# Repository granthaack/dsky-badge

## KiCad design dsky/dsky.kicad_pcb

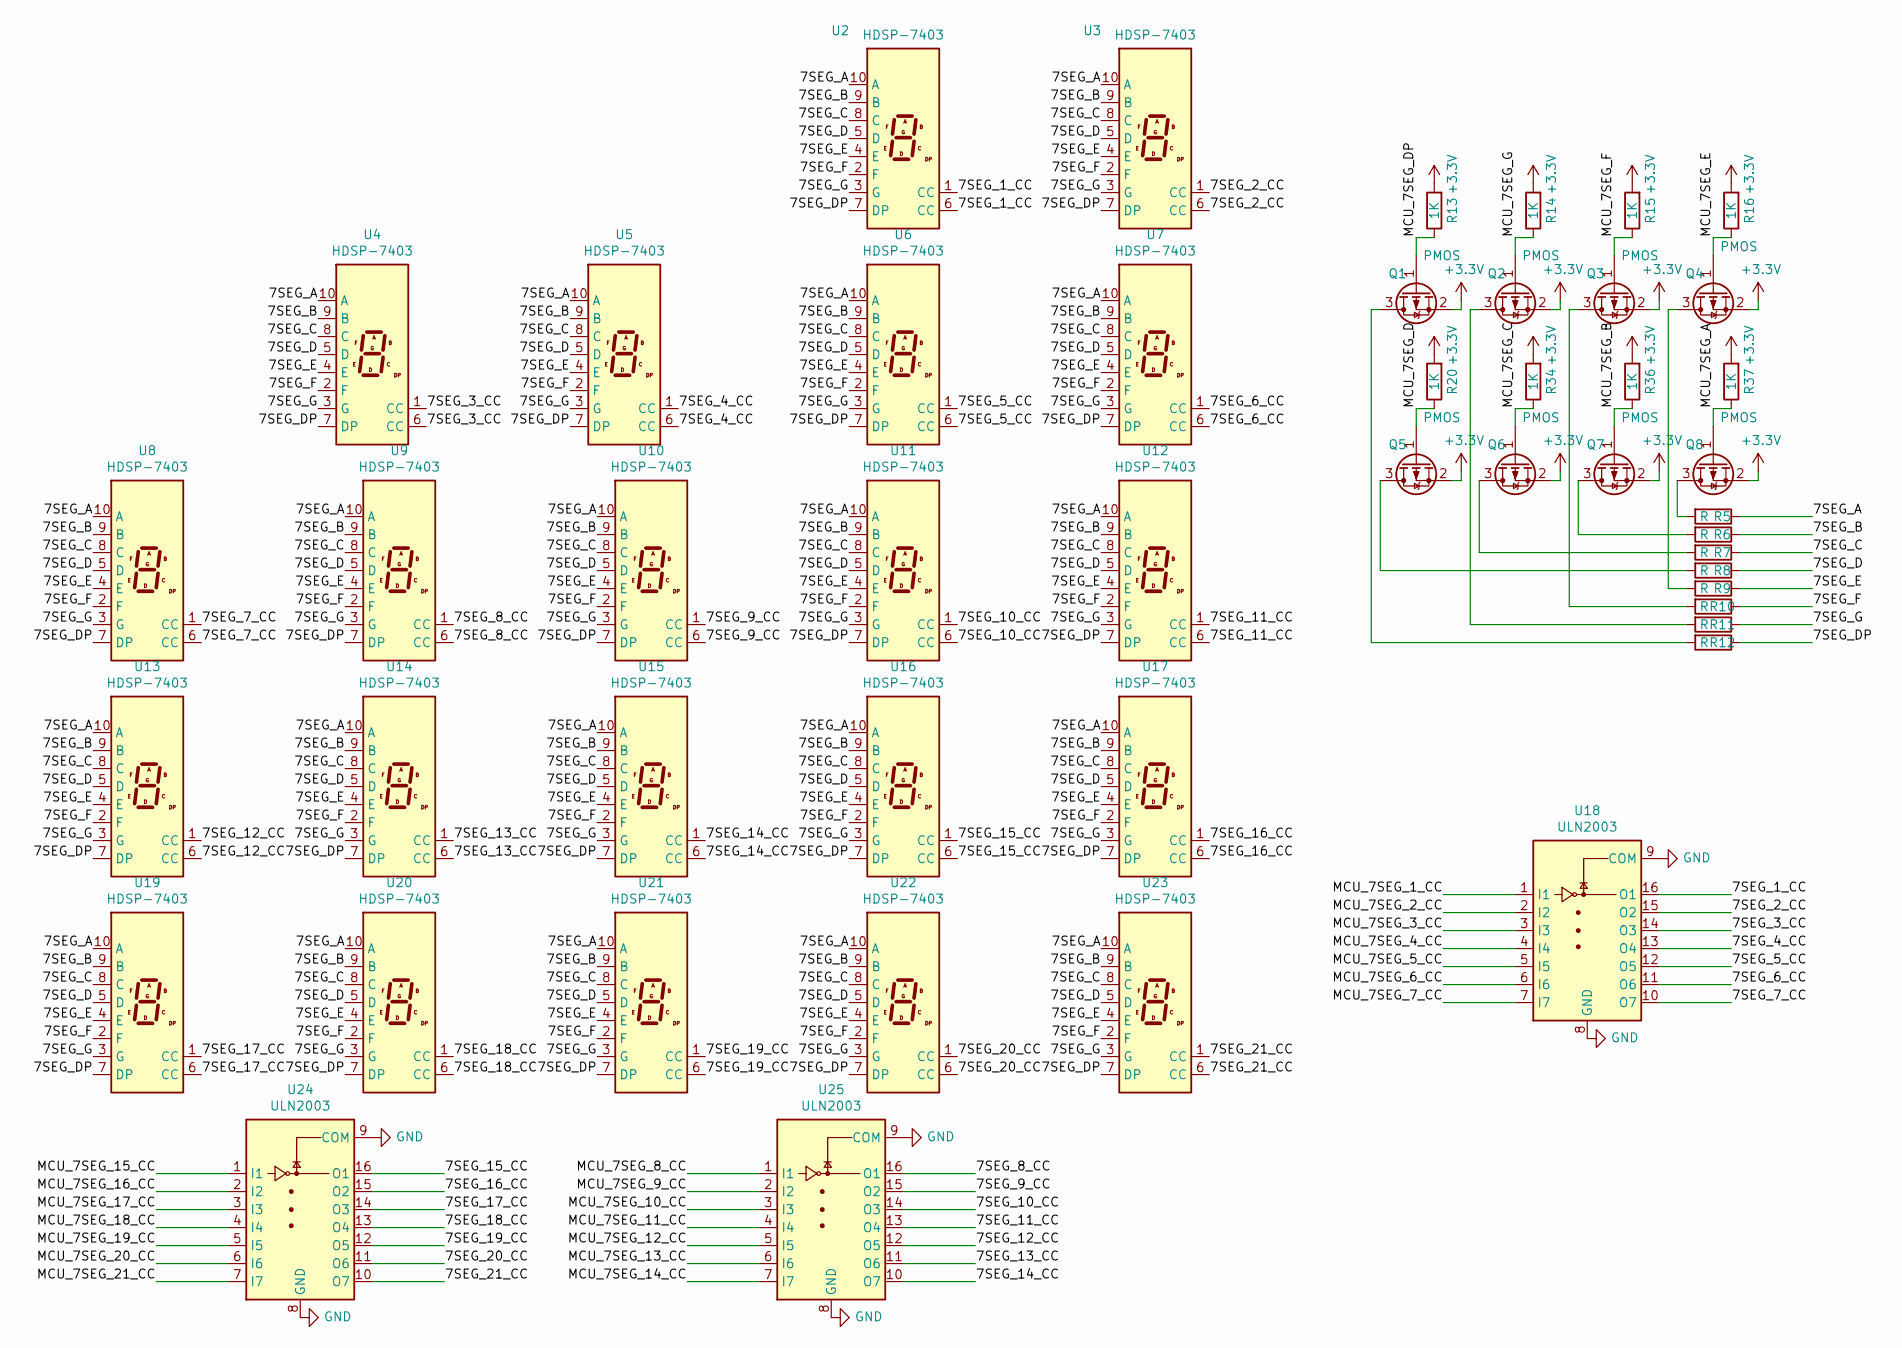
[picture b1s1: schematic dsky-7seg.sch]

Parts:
Q1, Q2, Q3, Q4, Q5, Q6, Q7, Q8: PMOS; SOT-23
R5, R6, R7, R8, R9, R10, R11, R12: R; R_0805_2012Metric
R13, R14, R15, R16, R20, R34, R36, R37: 1K; R_0402_1005Metric
U2, U3, U4, U5, U6, U7, U8, U9, U10, U11, U12, U13, U14, U15, U16, U17, U19, U20, U21, U22, U23: HDSP-7403; HDSP-7401
U18, U24, U25: ULN2003; SOIC-16_3.9x9.9mm_P1.27mm

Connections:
/dsky-7seg/7SEG_1_CC: U2.1 (CC), U2.6 (CC), U18.16 (O1)
/dsky-7seg/7SEG_2_CC: U3.1 (CC), U3.6 (CC), U18.15 (O2)
/dsky-7seg/7SEG_3_CC: U4.1 (CC), U4.6 (CC), U18.14 (O3)
/dsky-7seg/7SEG_4_CC: U5.1 (CC), U5.6 (CC), U18.13 (O4)
/dsky-7seg/7SEG_5_CC: U6.1 (CC), U6.6 (CC), U18.12 (O5)
/dsky-7seg/7SEG_6_CC: U7.1 (CC), U7.6 (CC), U18.11 (O6)
/dsky-7seg/7SEG_7_CC: U8.1 (CC), U8.6 (CC), U18.10 (O7)
/dsky-7seg/7SEG_8_CC: U9.1 (CC), U9.6 (CC), U25.16 (O1)
/dsky-7seg/7SEG_9_CC: U10.1 (CC), U10.6 (CC), U25.15 (O2)
/dsky-7seg/7SEG_10_CC: U11.1 (CC), U11.6 (CC), U25.14 (O3)
/dsky-7seg/7SEG_11_CC: U12.1 (CC), U12.6 (CC), U25.13 (O4)
/dsky-7seg/7SEG_12_CC: U13.1 (CC), U13.6 (CC), U25.12 (O5)
/dsky-7seg/7SEG_13_CC: U14.1 (CC), U14.6 (CC), U25.11 (O6)
/dsky-7seg/7SEG_14_CC: U15.1 (CC), U15.6 (CC), U25.10 (O7)
/dsky-7seg/7SEG_15_CC: U16.1 (CC), U16.6 (CC), U24.16 (O1)
/dsky-7seg/7SEG_16_CC: U17.1 (CC), U17.6 (CC), U24.15 (O2)
/dsky-7seg/7SEG_17_CC: U19.1 (CC), U19.6 (CC), U24.14 (O3)
/dsky-7seg/7SEG_18_CC: U20.1 (CC), U20.6 (CC), U24.13 (O4)
/dsky-7seg/7SEG_19_CC: U21.1 (CC), U21.6 (CC), U24.12 (O5)
/dsky-7seg/7SEG_20_CC: U22.1 (CC), U22.6 (CC), U24.11 (O6)
/dsky-7seg/7SEG_21_CC: U23.1 (CC), U23.6 (CC), U24.10 (O7)
/dsky-7seg/7SEG_A: R5.1, U2.10 (A), U3.10 (A), U4.10 (A), U5.10 (A), U6.10 (A), U7.10 (A), U8.10 (A), U9.10 (A), U10.10 (A), U11.10 (A), U12.10 (A), U13.10 (A), U14.10 (A), U15.10 (A), U16.10 (A), U17.10 (A), U19.10 (A), U20.10 (A), U21.10 (A), U22.10 (A), U23.10 (A)
/dsky-7seg/7SEG_B: R6.1, U2.9 (B), U3.9 (B), U4.9 (B), U5.9 (B), U6.9 (B), U7.9 (B), U8.9 (B), U9.9 (B), U10.9 (B), U11.9 (B), U12.9 (B), U13.9 (B), U14.9 (B), U15.9 (B), U16.9 (B), U17.9 (B), U19.9 (B), U20.9 (B), U21.9 (B), U22.9 (B), U23.9 (B)
/dsky-7seg/7SEG_C: R7.1, U2.8 (C), U3.8 (C), U4.8 (C), U5.8 (C), U6.8 (C), U7.8 (C), U8.8 (C), U9.8 (C), U10.8 (C), U11.8 (C), U12.8 (C), U13.8 (C), U14.8 (C), U15.8 (C), U16.8 (C), U17.8 (C), U19.8 (C), U20.8 (C), U21.8 (C), U22.8 (C), U23.8 (C)
/dsky-7seg/7SEG_D: R8.1, U2.5 (D), U3.5 (D), U4.5 (D), U5.5 (D), U6.5 (D), U7.5 (D), U8.5 (D), U9.5 (D), U10.5 (D), U11.5 (D), U12.5 (D), U13.5 (D), U14.5 (D), U15.5 (D), U16.5 (D), U17.5 (D), U19.5 (D), U20.5 (D), U21.5 (D), U22.5 (D), U23.5 (D)
/dsky-7seg/7SEG_DP: R12.1, U2.7 (DP), U3.7 (DP), U4.7 (DP), U5.7 (DP), U6.7 (DP), U7.7 (DP), U8.7 (DP), U9.7 (DP), U10.7 (DP), U11.7 (DP), U12.7 (DP), U13.7 (DP), U14.7 (DP), U15.7 (DP), U16.7 (DP), U17.7 (DP), U19.7 (DP), U20.7 (DP), U21.7 (DP), U22.7 (DP), U23.7 (DP)
/dsky-7seg/7SEG_E: R9.1, U2.4 (E), U3.4 (E), U4.4 (E), U5.4 (E), U6.4 (E), U7.4 (E), U8.4 (E), U9.4 (E), U10.4 (E), U11.4 (E), U12.4 (E), U13.4 (E), U14.4 (E), U15.4 (E), U16.4 (E), U17.4 (E), U19.4 (E), U20.4 (E), U21.4 (E), U22.4 (E), U23.4 (E)
/dsky-7seg/7SEG_F: R10.1, U2.2 (F), U3.2 (F), U4.2 (F), U5.2 (F), U6.2 (F), U7.2 (F), U8.2 (F), U9.2 (F), U10.2 (F), U11.2 (F), U12.2 (F), U13.2 (F), U14.2 (F), U15.2 (F), U16.2 (F), U17.2 (F), U19.2 (F), U20.2 (F), U21.2 (F), U22.2 (F), U23.2 (F)
/dsky-7seg/7SEG_G: R11.1, U2.3 (G), U3.3 (G), U4.3 (G), U5.3 (G), U6.3 (G), U7.3 (G), U8.3 (G), U9.3 (G), U10.3 (G), U11.3 (G), U12.3 (G), U13.3 (G), U14.3 (G), U15.3 (G), U16.3 (G), U17.3 (G), U19.3 (G), U20.3 (G), U21.3 (G), U22.3 (G), U23.3 (G)
/dsky-7seg/MCU_7SEG_1_CC: U18.1 (I1)
/dsky-7seg/MCU_7SEG_2_CC: U18.2 (I2)
/dsky-7seg/MCU_7SEG_3_CC: U18.3 (I3)
/dsky-7seg/MCU_7SEG_4_CC: U18.4 (I4)
/dsky-7seg/MCU_7SEG_5_CC: U18.5 (I5)
/dsky-7seg/MCU_7SEG_6_CC: U18.6 (I6)
/dsky-7seg/MCU_7SEG_7_CC: U18.7 (I7)
/dsky-7seg/MCU_7SEG_8_CC: U25.1 (I1)
/dsky-7seg/MCU_7SEG_9_CC: U25.2 (I2)
/dsky-7seg/MCU_7SEG_10_CC: U25.3 (I3)
/dsky-7seg/MCU_7SEG_11_CC: U25.4 (I4)
/dsky-7seg/MCU_7SEG_12_CC: U25.5 (I5)
/dsky-7seg/MCU_7SEG_13_CC: U25.6 (I6)
/dsky-7seg/MCU_7SEG_14_CC: U25.7 (I7)
/dsky-7seg/MCU_7SEG_15_CC: U24.1 (I1)
/dsky-7seg/MCU_7SEG_16_CC: U24.2 (I2)
/dsky-7seg/MCU_7SEG_17_CC: U24.3 (I3)
/dsky-7seg/MCU_7SEG_18_CC: U24.4 (I4)
/dsky-7seg/MCU_7SEG_19_CC: U24.5 (I5)
/dsky-7seg/MCU_7SEG_20_CC: U24.6 (I6)
/dsky-7seg/MCU_7SEG_21_CC: U24.7 (I7)
/dsky-7seg/MCU_7SEG_A: Q8.1 (G), R37.1
/dsky-7seg/MCU_7SEG_B: Q7.1 (G), R36.1
/dsky-7seg/MCU_7SEG_C: Q6.1 (G), R34.1
/dsky-7seg/MCU_7SEG_DP: Q1.1 (G), R13.1
/dsky-7seg/MCU_7SEG_E: Q4.1 (G), R16.1
/dsky-7seg/MCU_7SEG_F: Q3.1 (G), R15.1
/dsky-7seg/MCU_7SEG_G: Q2.1 (G), R14.1
unnamed: Q1.3 (D), R12.2
unnamed: Q2.3 (D), R11.2
unnamed: Q3.3 (D), R10.2
unnamed: Q4.3 (D), R9.2
unnamed: Q5.3 (D), R8.2
unnamed: Q6.3 (D), R7.2
unnamed: Q7.3 (D), R6.2
unnamed: Q8.3 (D), R5.2

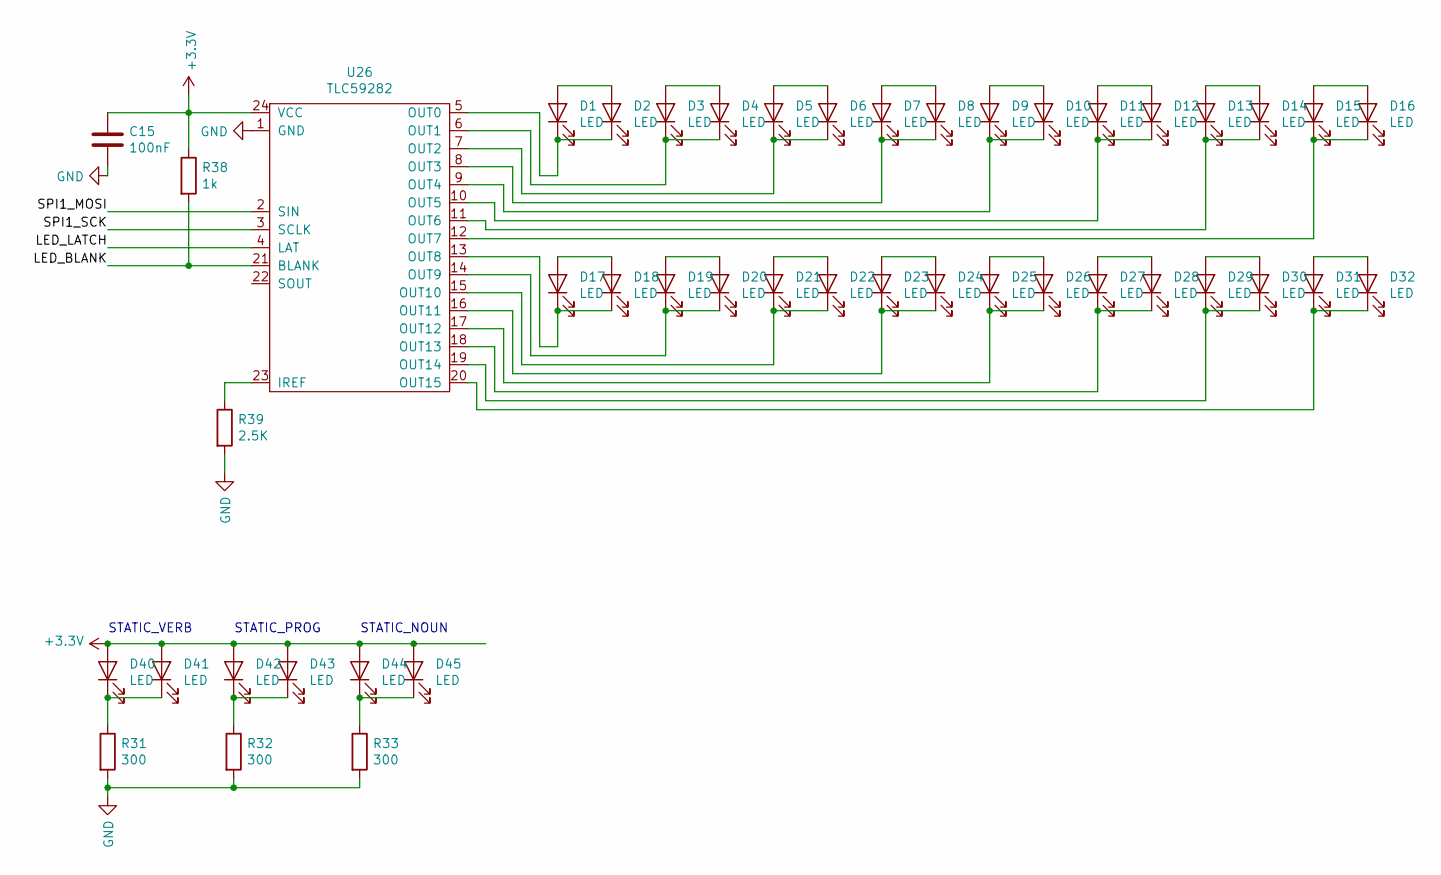
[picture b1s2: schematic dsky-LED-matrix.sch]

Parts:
C15: 100nF; C_0402_1005Metric
D1, D2, D3, D4, D5, D6, D7, D8, D9, D10, D11, D12, D13, D14, D15, D16, D17, D18, D19, D20, D21, D22, D23, D24, D25, D26: LED; 3.00x1.50_RIGHT_LED
D27, D28, D29, D30, D31, D32, D40, D41, D42, D43, D44, D45: LED; 2.00x0.50_RIGHT_LED
R31, R32, R33: 300; R_0603_1608Metric
R38: 1k; R_0402_1005Metric
R39: 2.5K; R_0402_1005Metric
U26: TLC59282; SSOP-24_3.9x8.7mm_P0.635mm

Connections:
/dsky-LED-matrix/LED_BLANK: R38.2, U26.21 (BLANK)
/dsky-LED-matrix/LED_LATCH: U26.4 (LAT)
/dsky-LED-matrix/SPI1_MOSI: U26.2 (SIN)
/dsky-LED-matrix/SPI1_SCK: U26.3 (SCLK)
unnamed: D1.1 (K), D2.1 (K), U26.5 (OUT0)
unnamed: D1.2 (A), D2.2 (A)
unnamed: D3.1 (K), D4.1 (K), U26.6 (OUT1)
unnamed: D3.2 (A), D4.2 (A)
unnamed: D5.1 (K), D6.1 (K), U26.7 (OUT2)
unnamed: D5.2 (A), D6.2 (A)
unnamed: D7.1 (K), D8.1 (K), U26.8 (OUT3)
unnamed: D7.2 (A), D8.2 (A)
unnamed: D9.1 (K), D10.1 (K), U26.9 (OUT4)
unnamed: D9.2 (A), D10.2 (A)
unnamed: D11.1 (K), D12.1 (K), U26.10 (OUT5)
unnamed: D11.2 (A), D12.2 (A)
unnamed: D13.1 (K), D14.1 (K), U26.11 (OUT6)
unnamed: D13.2 (A), D14.2 (A)
unnamed: D15.1 (K), D16.1 (K), U26.12 (OUT7)
unnamed: D15.2 (A), D16.2 (A)
unnamed: D17.1 (K), D18.1 (K), U26.13 (OUT8)
unnamed: D17.2 (A), D18.2 (A)
unnamed: D19.1 (K), D20.1 (K), U26.14 (OUT9)
unnamed: D19.2 (A), D20.2 (A)
unnamed: D21.1 (K), D22.1 (K), U26.15 (OUT10)
unnamed: D21.2 (A), D22.2 (A)
unnamed: D23.1 (K), D24.1 (K), U26.16 (OUT11)
unnamed: D23.2 (A), D24.2 (A)
unnamed: D25.1 (K), D26.1 (K), U26.17 (OUT12)
unnamed: D25.2 (A), D26.2 (A)
unnamed: D27.1 (K), D28.1 (K), U26.18 (OUT13)
unnamed: D27.2 (A), D28.2 (A)
unnamed: D29.1 (K), D30.1 (K), U26.19 (OUT14)
unnamed: D29.2 (A), D30.2 (A)
unnamed: D31.1 (K), D32.1 (K), U26.20 (OUT15)
unnamed: D31.2 (A), D32.2 (A)
unnamed: D40.1 (K), D41.1 (K), R31.1
unnamed: D42.1 (K), D43.1 (K), R32.1
unnamed: D44.1 (K), D45.1 (K), R33.1
unnamed: R39.1, U26.23 (IREF)

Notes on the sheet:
STATIC_VERB
STATIC_PROG
STATIC_NOUN

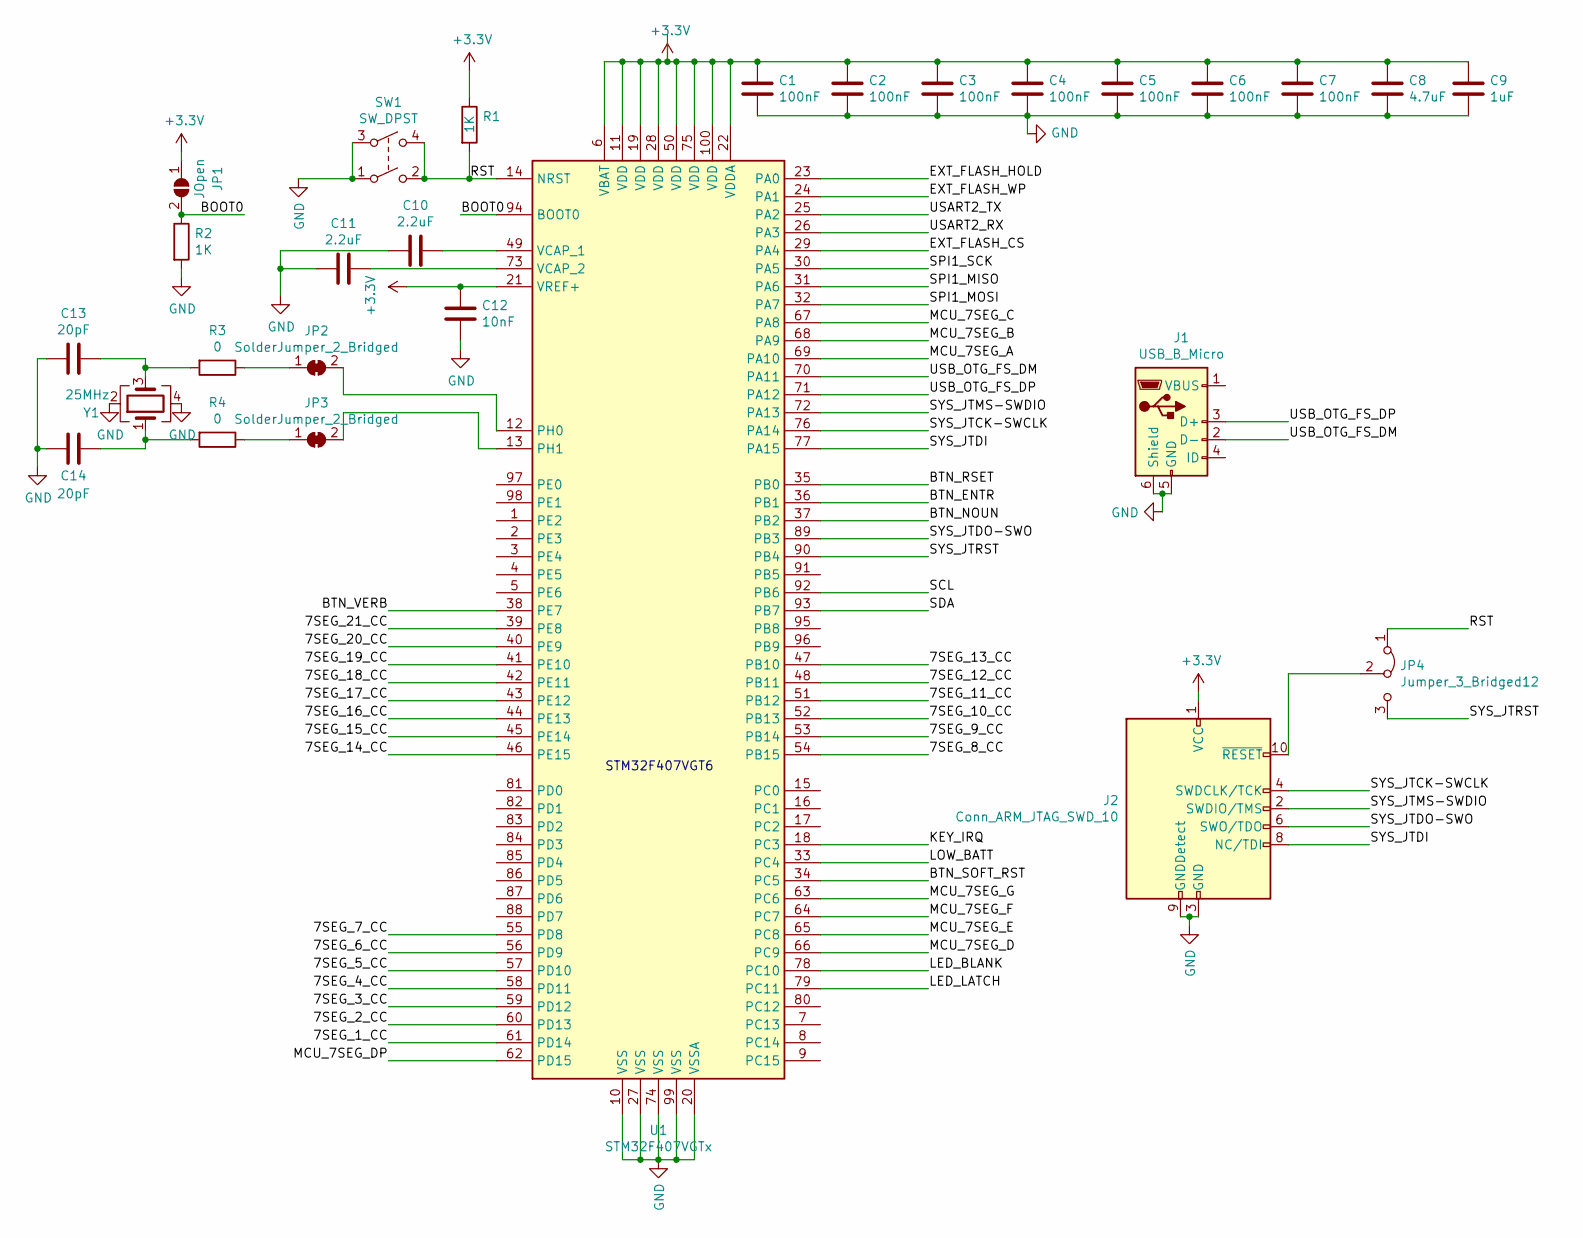
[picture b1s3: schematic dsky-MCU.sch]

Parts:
C1, C2, C3, C4, C5, C6, C7: 100nF; C_0402_1005Metric
C8: 4.7uF; C_0805_2012Metric
C9: 1uF; C_0805_2012Metric
C10, C11: 2.2uF; C_0805_2012Metric
C12: 10nF; C_0603_1608Metric
C13, C14: 20pF; C_0603_1608Metric
J1: USB_B_Micro; USB_Micro-B_Molex-105017-0001
J2: Conn_ARM_JTAG_SWD_10; PinHeader_2x05_P1.27mm_Vertical_SMD
JP1: JOpen; SolderJumper-2_P1.3mm_Open_RoundedPad1.0x1.5mm
JP2, JP3: SolderJumper_2_Bridged; SolderJumper-2_P1.3mm_Bridged2Bar_RoundedPad1.0x1.5mm
JP4: Jumper_3_Bridged12; SolderJumper-3_P1.3mm_Bridged2Bar12_RoundedPad1.0x1.5mm
R1, R2: 1K; R_0402_1005Metric
R3, R4: 0; R_0402_1005Metric
SW1: SW_DPST; SW_SPST_FSMSM
U1: STM32F407VGTx; LQFP-100_14x14mm_P0.5mm
Y1: 25MHz; Crystal_SMD_3225-4Pin_3.2x2.5mm

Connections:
/dsky-MCU/7SEG_1_CC: U1.61 (PD14)
/dsky-MCU/7SEG_2_CC: U1.60 (PD13)
/dsky-MCU/7SEG_3_CC: U1.59 (PD12)
/dsky-MCU/7SEG_4_CC: U1.58 (PD11)
/dsky-MCU/7SEG_5_CC: U1.57 (PD10)
/dsky-MCU/7SEG_6_CC: U1.56 (PD9)
/dsky-MCU/7SEG_7_CC: U1.55 (PD8)
/dsky-MCU/7SEG_8_CC: U1.54 (PB15)
/dsky-MCU/7SEG_9_CC: U1.53 (PB14)
/dsky-MCU/7SEG_10_CC: U1.52 (PB13)
/dsky-MCU/7SEG_11_CC: U1.51 (PB12)
/dsky-MCU/7SEG_12_CC: U1.48 (PB11)
/dsky-MCU/7SEG_13_CC: U1.47 (PB10)
/dsky-MCU/7SEG_14_CC: U1.46 (PE15)
/dsky-MCU/7SEG_15_CC: U1.45 (PE14)
/dsky-MCU/7SEG_16_CC: U1.44 (PE13)
/dsky-MCU/7SEG_17_CC: U1.43 (PE12)
/dsky-MCU/7SEG_18_CC: U1.42 (PE11)
/dsky-MCU/7SEG_19_CC: U1.41 (PE10)
/dsky-MCU/7SEG_20_CC: U1.40 (PE9)
/dsky-MCU/7SEG_21_CC: U1.39 (PE8)
/dsky-MCU/BOOT0: JP1.2 (B), R2.1, U1.94 (BOOT0)
/dsky-MCU/BTN_ENTR: U1.36 (PB1)
/dsky-MCU/BTN_NOUN: U1.37 (PB2)
/dsky-MCU/BTN_RSET: U1.35 (PB0)
/dsky-MCU/BTN_SOFT_RST: U1.34 (PC5)
/dsky-MCU/BTN_VERB: U1.38 (PE7)
/dsky-MCU/EXT_FLASH_CS: U1.29 (PA4)
/dsky-MCU/EXT_FLASH_HOLD: U1.23 (PA0)
/dsky-MCU/EXT_FLASH_WP: U1.24 (PA1)
/dsky-MCU/KEY_IRQ: U1.18 (PC3)
/dsky-MCU/LED_BLANK: U1.78 (PC10)
/dsky-MCU/LED_LATCH: U1.79 (PC11)
/dsky-MCU/LOW_BATT: U1.33 (PC4)
/dsky-MCU/MCU_7SEG_A: U1.69 (PA10)
/dsky-MCU/MCU_7SEG_B: U1.68 (PA9)
/dsky-MCU/MCU_7SEG_C: U1.67 (PA8)
/dsky-MCU/MCU_7SEG_D: U1.66 (PC9)
/dsky-MCU/MCU_7SEG_DP: U1.62 (PD15)
/dsky-MCU/MCU_7SEG_E: U1.65 (PC8)
/dsky-MCU/MCU_7SEG_F: U1.64 (PC7)
/dsky-MCU/MCU_7SEG_G: U1.63 (PC6)
/dsky-MCU/RST: JP4.1 (A), R1.2, SW1.2, SW1.4, U1.14 (NRST)
/dsky-MCU/SCL: U1.92 (PB6)
/dsky-MCU/SDA: U1.93 (PB7)
/dsky-MCU/SPI1_MISO: U1.31 (PA6)
/dsky-MCU/SPI1_MOSI: U1.32 (PA7)
/dsky-MCU/SPI1_SCK: U1.30 (PA5)
/dsky-MCU/SYS_JTCK-SWCLK: J2.4 (SWDCLK/TCK), U1.76 (PA14)
/dsky-MCU/SYS_JTDI: J2.8 (NC/TDI), U1.77 (PA15)
/dsky-MCU/SYS_JTDO-SWO: J2.6 (SWO/TDO), U1.89 (PB3)
/dsky-MCU/SYS_JTMS-SWDIO: J2.2 (SWDIO/TMS), U1.72 (PA13)
/dsky-MCU/SYS_JTRST: JP4.3 (B), U1.90 (PB4)
/dsky-MCU/USART2_RX: U1.26 (PA3)
/dsky-MCU/USART2_TX: U1.25 (PA2)
/dsky-MCU/USB_OTG_FS_DM: J1.2 (D-), U1.70 (PA11)
/dsky-MCU/USB_OTG_FS_DP: J1.3 (D+), U1.71 (PA12)
unnamed: C10.1, U1.49 (VCAP_1)
unnamed: C11.1, U1.73 (VCAP_2)
unnamed: C13.1, R3.2, Y1.3
unnamed: C14.1, R4.2, Y1.1
unnamed: J2.10 (~RESET~), JP4.2 (C)
unnamed: JP2.1 (A), R3.1
unnamed: JP2.2 (B), U1.12 (PH0)
unnamed: JP3.1 (A), R4.1
unnamed: JP3.2 (B), U1.13 (PH1)

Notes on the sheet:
STM32F407VGT6

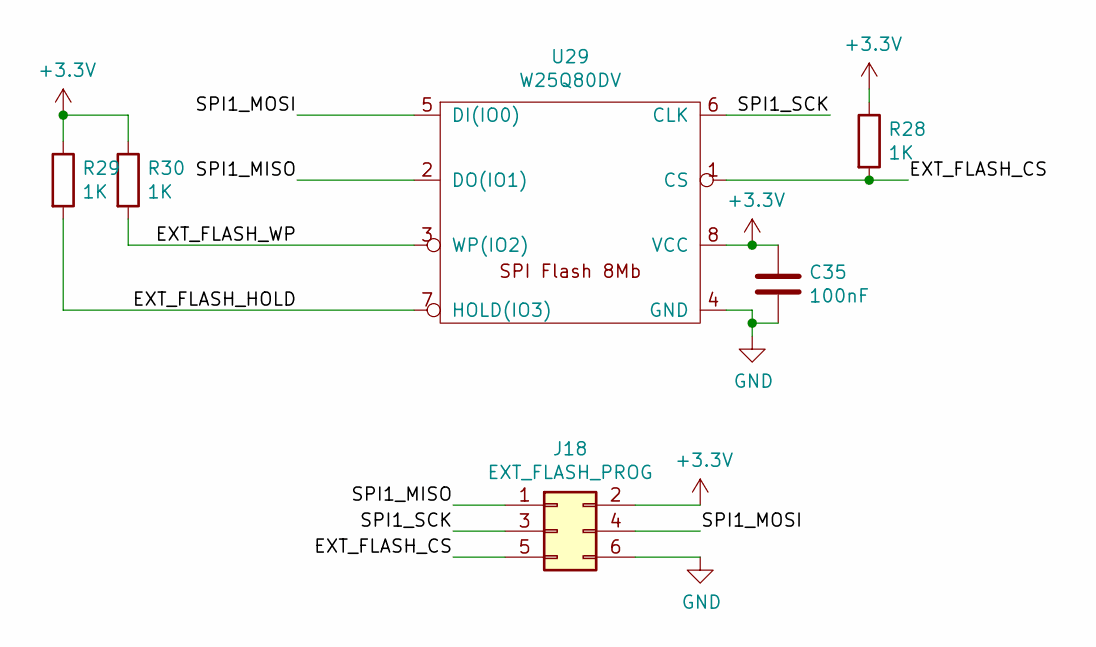
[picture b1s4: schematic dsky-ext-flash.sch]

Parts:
C35: 100nF; C_0603_1608Metric
J18: EXT_FLASH_PROG; PinHeader_2x03_P2.54mm_Vertical_SMD
R28, R29, R30: 1K; R_0603_1608Metric
U29: W25Q80DV

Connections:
/dsky-ext-flash/EXT_FLASH_CS: J18.5, R28.2, U29.1 (CS)
/dsky-ext-flash/EXT_FLASH_HOLD: R29.2, U29.7 (HOLD(IO3))
/dsky-ext-flash/EXT_FLASH_WP: R30.2, U29.3 (WP(IO2))
/dsky-ext-flash/SPI1_MISO: J18.1, U29.2 (DO(IO1))
/dsky-ext-flash/SPI1_MOSI: J18.4, U29.5 (DI(IO0))
/dsky-ext-flash/SPI1_SCK: J18.3, U29.6 (CLK)

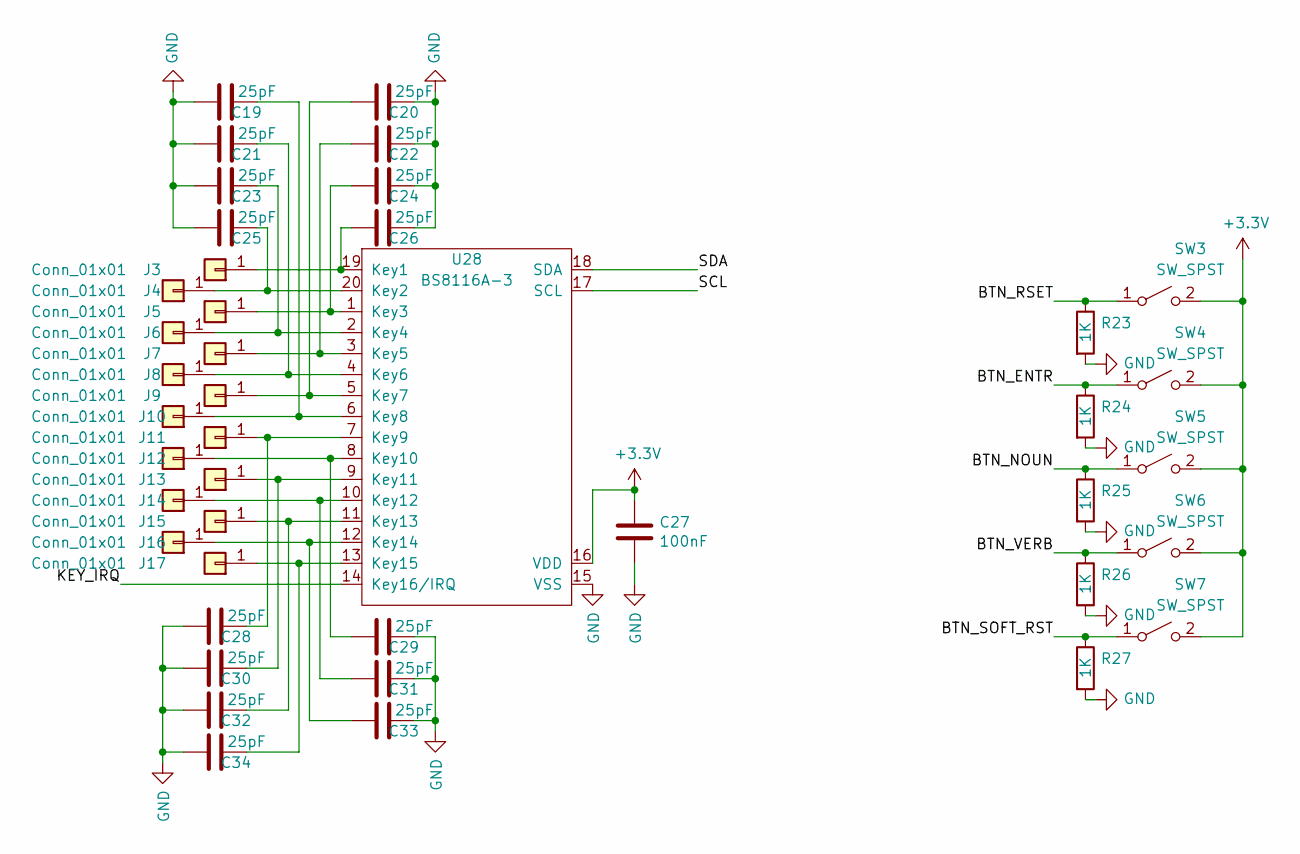
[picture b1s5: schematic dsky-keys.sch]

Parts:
C19, C20, C21, C22, C23, C24, C25, C26, C28, C29, C30, C31, C32, C33, C34: 25pF; C_0402_1005Metric
C27: 100nF; C_0603_1608Metric
J3, J4, J5, J6, J7, J8, J9, J10, J11, J12, J13, J14, J15, J16, J17: Conn_01x01; TestPoint_Pad_D1.0mm
R23, R24, R25, R26, R27: 1K; R_0603_1608Metric
SW3, SW4, SW5, SW6, SW7: SW_SPST; SW_SPST_FSMSM
U28: BS8116A-3

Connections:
/dsky-keys/BTN_ENTR: R24.1, SW4.1 (A)
/dsky-keys/BTN_NOUN: R25.1, SW5.1 (A)
/dsky-keys/BTN_RSET: R23.1, SW3.1 (A)
/dsky-keys/BTN_SOFT_RST: R27.1, SW7.1 (A)
/dsky-keys/BTN_VERB: R26.1, SW6.1 (A)
/dsky-keys/KEY_IRQ: U28.14 (Key16/IRQ)
/dsky-keys/SCL: U28.17 (SCL)
/dsky-keys/SDA: U28.18 (SDA)
unnamed: C19.2, J10.1, U28.6 (Key8)
unnamed: C20.1, J9.1, U28.5 (Key7)
unnamed: C21.2, J8.1, U28.4 (Key6)
unnamed: C22.1, J7.1, U28.3 (Key5)
unnamed: C23.2, J6.1, U28.2 (Key4)
unnamed: C24.1, J5.1, U28.1 (Key3)
unnamed: C25.2, J4.1, U28.20 (Key2)
unnamed: C26.1, J3.1, U28.19 (Key1)
unnamed: C28.2, J11.1, U28.7 (Key9)
unnamed: C29.1, J12.1, U28.8 (Key10)
unnamed: C30.2, J13.1, U28.9 (Key11)
unnamed: C31.1, J14.1, U28.10 (Key12)
unnamed: C32.2, J15.1, U28.11 (Key13)
unnamed: C33.1, J16.1, U28.12 (Key14)
unnamed: C34.2, J17.1, U28.13 (Key15)

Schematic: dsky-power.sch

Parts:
BT1: Battery; PinHeader_1x02_P2.54mm_Vertical
C16: 2.2uF; C_0805_2012Metric
C17: 47uF; C_1206_3216Metric
C18: 10uF; C_1206_3216Metric
D39: LED; 3.00x1.50_RIGHT_LED
F1: Polyfuse; Fuse_1210_3225Metric
L1: 6.8uH; L_Bourns-SRN4018
Q9: PMOS; SOT-23
R17: 1M; R_0603_1608Metric
R18: 1K; R_0603_1608Metric
R19: 1.4M; R_0603_1608Metric
R20: 180K; R_0603_1608Metric
R21: 390K; R_0603_1608Metric
R22: 300; R_0805_2012Metric
U27: TPS61020

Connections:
/dsky-power/LOW_BATT: Q9.1 (G), R18.2, U27.3
unnamed 133: BT1.1 (+); also elsewhere on the board
unnamed: BT1.2 (-), F1.2
unnamed: D39.1 (K), R22.1
unnamed: L1.2, U27.7
unnamed: Q9.2 (S), R22.2
unnamed: R19.2, R21.1, U27.2

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
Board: 2 copper layers, 183 parts (0 on the bottom side), 138 nets, no tracks yet.

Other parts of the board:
R35: 0; R_0402_1005Metric

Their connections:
unnamed 133: R35.2; also elsewhere on the board

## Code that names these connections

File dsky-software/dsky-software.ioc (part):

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Mcu.Name=STM32F407V(E-G)Tx
Mcu.Package=LQFP100
Mcu.UserName=STM32F407VGTx
PA0-WKUP.GPIOParameters=GPIO_Label
PA0-WKUP.GPIO_Label=EXT_FLASH_HOLD
PA0-WKUP.Signal=GPIO_Output
PA1.GPIOParameters=GPIO_Label
PA1.GPIO_Label=EXT_FLASH_WP
PA1.Signal=GPIO_Output
PA10.GPIOParameters=GPIO_Label
PA10.GPIO_Label=SEG7_A
PA10.Signal=GPIO_Output
PA11.Mode=Device_Only
PA11.Signal=USB_OTG_FS_DM
PA12.Mode=Device_Only
PA12.Signal=USB_OTG_FS_DP
PA13.Mode=JTAG_5_pins
PA13.Signal=SYS_JTMS-SWDIO
PA14.Mode=JTAG_5_pins
PA14.Signal=SYS_JTCK-SWCLK
PA15.Mode=JTAG_5_pins
PA15.Signal=SYS_JTDI
PA2.Mode=Asynchronous
PA2.Signal=USART2_TX
PA3.Mode=Asynchronous
PA3.Signal=USART2_RX
PA4.GPIOParameters=GPIO_Label
PA4.GPIO_Label=EXT_FLASH_CS
PA4.Signal=GPIO_Output
PA5.Mode=Full_Duplex_Master
PA5.Signal=SPI1_SCK
PA6.Mode=Full_Duplex_Master
PA6.Signal=SPI1_MISO
PA7.Mode=Full_Duplex_Master
PA7.Signal=SPI1_MOSI
PA8.GPIOParameters=GPIO_Label
PA8.GPIO_Label=SEG7_C
PA8.Signal=GPIO_Output
PA9.GPIOParameters=GPIO_Label
PA9.GPIO_Label=SEG7_B
PA9.Signal=GPIO_Output
PB0.GPIOParameters=GPIO_Label
PB0.GPIO_Label=BTN_RSET
PB0.Signal=GPXTI0
PB1.GPIOParameters=GPIO_Label
PB1.GPIO_Label=BTN_ENTR
PB1.Signal=GPXTI1
PB10.GPIOParameters=GPIO_Label
PB10.GPIO_Label=SEG7_13
PB10.Signal=GPIO_Output
PB11.GPIOParameters=GPIO_Label
PB11.GPIO_Label=SEG7_12
PB11.Signal=GPIO_Output
PB12.GPIOParameters=GPIO_Label
PB12.GPIO_Label=SEG7_11
PB12.Signal=GPIO_Output
PB13.GPIOParameters=GPIO_Label
PB13.GPIO_Label=SEG7_10
PB13.Signal=GPIO_Output
PB14.GPIOParameters=GPIO_Label
PB14.GPIO_Label=SEG7_9
PB14.Signal=GPIO_Output
PB15.GPIOParameters=GPIO_Label
PB15.GPIO_Label=SEG7_8
PB15.Signal=GPIO_Output
PB2.GPIOParameters=GPIO_Label
PB2.GPIO_Label=BTN_NOUN
PB2.Signal=GPXTI2
PB3.Mode=JTAG_5_pins
PB3.Signal=SYS_JTDO-SWO
PB4.Mode=JTAG_5_pins
PB4.Signal=SYS_JTRST
PB6.Mode=I2C
PB6.Signal=I2C1_SCL
PB7.Mode=I2C
PB7.Signal=I2C1_SDA
PC10.GPIOParameters=GPIO_Label
PC10.GPIO_Label=LED_BLANK
PC10.Signal=GPIO_Output
PC11.GPIOParameters=GPIO_Label
PC11.GPIO_Label=LED_LATCH
PC11.Signal=GPIO_Output
PC3.GPIOParameters=GPIO_Label
PC3.GPIO_Label=KEY_IRQ
PC3.Signal=GPXTI3
PC4.GPIOParameters=GPIO_Label
PC4.GPIO_Label=LOW_BATT
PC4.Signal=GPIO_Input
PC5.GPIOParameters=GPIO_Label
PC5.GPIO_Label=BTN_SOFT_RST
PC5.Signal=GPXTI5
PC6.GPIOParameters=GPIO_Label
PC6.GPIO_Label=SEG7_G
PC6.Signal=GPIO_Output
PC7.GPIOParameters=GPIO_Label
PC7.GPIO_Label=SEG7_F
PC7.Signal=GPIO_Output
PC8.GPIOParameters=GPIO_Label
PC8.GPIO_Label=SEG7_E
PC8.Signal=GPIO_Output
PC9.GPIOParameters=GPIO_Label
PC9.GPIO_Label=SEG7_D
PC9.Signal=GPIO_Output
PD10.GPIOParameters=GPIO_Label
PD10.GPIO_Label=SEG7_5
PD10.Signal=GPIO_Output
PD11.GPIOParameters=GPIO_Label
PD11.GPIO_Label=SEG7_4
PD11.Signal=GPIO_Output
PD12.GPIOParameters=GPIO_Label
PD12.GPIO_Label=SEG7_3
PD12.Signal=GPIO_Output
PD13.GPIOParameters=GPIO_Label
PD13.GPIO_Label=SEG7_2
PD13.Signal=GPIO_Output
PD14.GPIOParameters=GPIO_Label
PD14.GPIO_Label=SEG7_1
PD14.Signal=GPIO_Output
PD15.GPIOParameters=GPIO_Label
PD15.GPIO_Label=SEG7_DP
PD15.Signal=GPIO_Output
PD8.GPIOParameters=GPIO_Label
PD8.GPIO_Label=SEG7_7
PD8.Signal=GPIO_Output
PD9.GPIOParameters=GPIO_Label
PD9.GPIO_Label=SEG7_6
PD9.Signal=GPIO_Output
PE10.GPIOParameters=GPIO_Label
PE10.GPIO_Label=SEG7_19
PE10.Signal=GPIO_Output
PE11.GPIOParameters=GPIO_Label
PE11.GPIO_Label=SEG7_18
PE11.Signal=GPIO_Output
PE12.GPIOParameters=GPIO_Label
PE12.GPIO_Label=SEG7_17
PE12.Signal=GPIO_Output
PE13.GPIOParameters=GPIO_Label
PE13.GPIO_Label=SEG7_16
PE13.Signal=GPIO_Output
PE14.GPIOParameters=GPIO_Label
PE14.GPIO_Label=SEG7_15
PE14.Signal=GPIO_Output
PE15.GPIOParameters=GPIO_Label
PE15.GPIO_Label=SEG7_14
PE15.Signal=GPIO_Output
PE7.GPIOParameters=GPIO_Label
PE7.GPIO_Label=BTN_VERB
PE7.Signal=GPXTI7
PE8.GPIOParameters=GPIO_Label
PE8.GPIO_Label=SEG7_21
PE8.Signal=GPIO_Output
PE9.GPIOParameters=GPIO_Label
PE9.GPIO_Label=SEG7_20
PE9.Signal=GPIO_Output
PH0-OSC_IN.Mode=HSE-External-Oscillator
PH0-OSC_IN.Signal=RCC_OSC_IN
PH1-OSC_OUT.Mode=HSE-External-Oscillator
PH1-OSC_OUT.Signal=RCC_OSC_OUT
RCC.HSE_VALUE=25000000
RCC.SYSCLKFreq_VALUE=120000000
RCC.SYSCLKSource=RCC_SYSCLKSOURCE_PLLCLK
board=custom

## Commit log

2020-10-19 playing around with linux for the stm32
2020-11-16 this hard drive is dying
